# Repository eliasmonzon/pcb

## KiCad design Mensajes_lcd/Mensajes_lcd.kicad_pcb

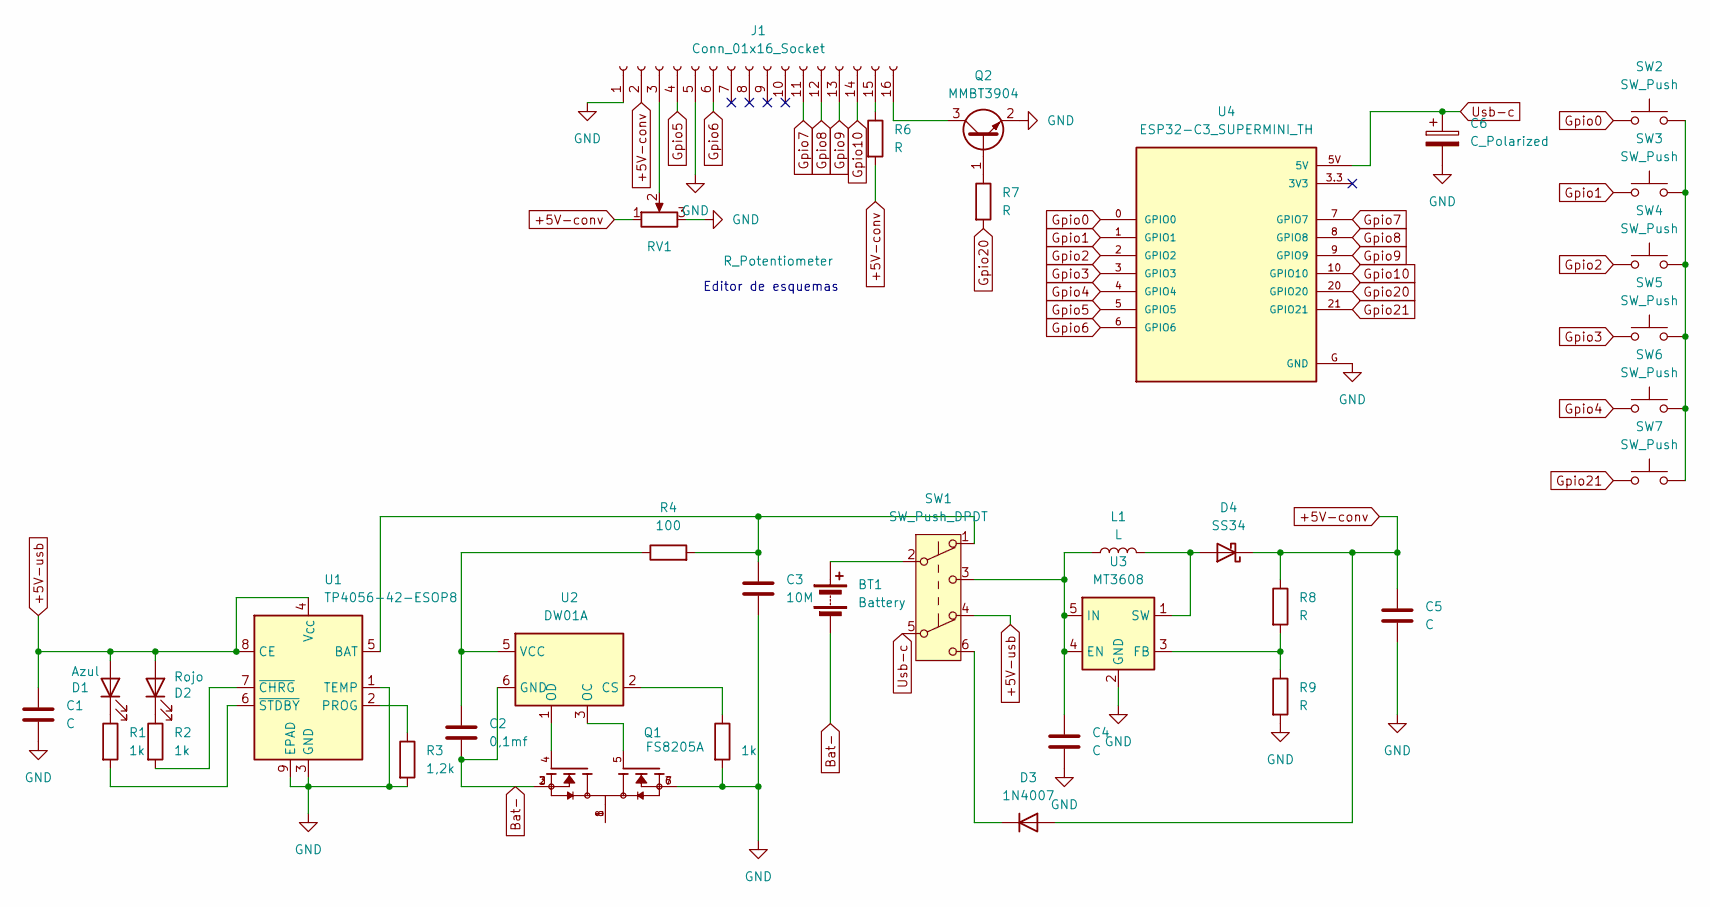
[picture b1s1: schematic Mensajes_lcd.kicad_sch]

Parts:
BT1: Battery; BatteryHolder_MPD_BH-18650-PC
C1, C4, C5: C; C_1206_3216Metric
C2: 0,1mf; C_1206_3216Metric
C3: 10M; C_1206_3216Metric
C6: C_Polarized; CP_Elec_3x5.3
D1: Azul; LED_D3.0mm
D2: Rojo; LED_D3.0mm
D3: 1N4007; D_1206_3216Metric_Pad1.42x1.75mm_HandSolder
D4: SS34; D_SMA
J1: Conn_01x16_Socket; PinHeader_1x16_P2.54mm_Vertical
L1: L; L_10.4x10.4_H4.8
Q1: FS8205A; TSSOP-8_4.4x3mm_P0.65mm; PARTREV 1.7
Q2: MMBT3904; SOT-23
R1, R2, R5: 1k; R_1206_3216Metric
R3: 1,2k; R_1206_3216Metric
R4: 100; R_1206_3216Metric
R6, R7, R8, R9: R; R_1206_3216Metric
RV1: R_Potentiometer; Potentiometer_Vishay_T73YP_Vertical
SW1: SW_Push_DPDT; SW_CK_JS202011AQN_DPDT_Angled
SW2, SW3, SW4, SW5, SW6, SW7: SW_Push; SW_SPST_Omron_B3F-40xx
U1: TP4056-42-ESOP8; SOIC-8-1EP_3.9x4.9mm_P1.27mm_EP2.29x3mm
U2: DW01A; SOT-23-6
U3: MT3608; SOT-23-6
U4: ESP32-C3_SUPERMINI_TH; MODULE_ESP32-C3_SUPERMINI_TH

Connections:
+5V-conv: C5.1, D3.2 (A), D4.1 (K), J1.2, R6.2, R8.1, RV1.1
+5V-usb: C1.1, D1.2 (A), D2.2 (A), SW1.4 (A), U1.4 (V_{CC}), U1.8 (CE)
Bat-: BT1.2 (-), C2.2, Q1.2, Q1.3, U2.6 (GND)
GND: C1.2, C3.2, C4.2, C5.2, C6.2, J1.1, J1.5, Q1.6, Q1.7, Q2.2 (E), R3.2, R5.2, R9.2, RV1.3, U1.1 (TEMP), U1.3 (GND), U1.9 (EPAD), U3.2 (GND), U4.G (GND)
Gpio0: SW2.1, U4.0 (GPIO0)
Gpio1: SW3.1, U4.1 (GPIO1)
Gpio2: SW4.1, U4.2 (GPIO2)
Gpio3: SW5.1, U4.3 (GPIO3)
Gpio4: SW6.1, U4.4 (GPIO4)
Gpio5: J1.4, U4.5 (GPIO5)
Gpio6: J1.6, U4.6 (GPIO6)
Gpio7: J1.11, U4.7 (GPIO7)
Gpio8: J1.12, U4.8 (GPIO8)
Gpio9: J1.13, U4.9 (GPIO9)
Gpio10: J1.14, U4.10 (GPIO10)
Gpio20: R7.2, U4.20 (GPIO20)
Gpio21: SW7.1, U4.21 (GPIO21)
unnamed: BT1.1 (+), SW1.2 (B)
unnamed: D1.1 (K), R1.1
unnamed: D2.1 (K), R2.1
unnamed: D3.1 (K), SW1.6 (C)
unnamed: D4.2 (A), L1.2, U3.1 (SW)
unnamed: J1.3, RV1.2
unnamed: J1.15, R6.1
unnamed: J1.16, Q2.3 (C)
unnamed: Q1.1, Q1.8
unnamed: Q2.1 (B), R7.1
unnamed: SW2.2, SW3.2, SW4.2, SW5.2, SW6.2, SW7.2
unnamed: C3.1, R4.2, SW1.1 (A), U1.5 (BAT)
unnamed: R3.1, U1.2 (PROG)
unnamed: R2.2, U1.7 (~CHRG)
unnamed: R1.2, U1.6 (~STDBY)
unnamed: R5.1, U2.2 (CS)
unnamed: Q1.5, U2.3 (OC)
unnamed: Q1.4, U2.1 (OD)
unnamed: C2.1, R4.1, U2.5 (VCC)
unnamed: C4.1, L1.1, SW1.3 (C), U3.4 (EN), U3.5 (IN)
unnamed: R8.2, R9.1, U3.3 (FB)
Usb-c: C6.1, SW1.5 (B), U4.5V

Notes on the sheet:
Editor de esquemas

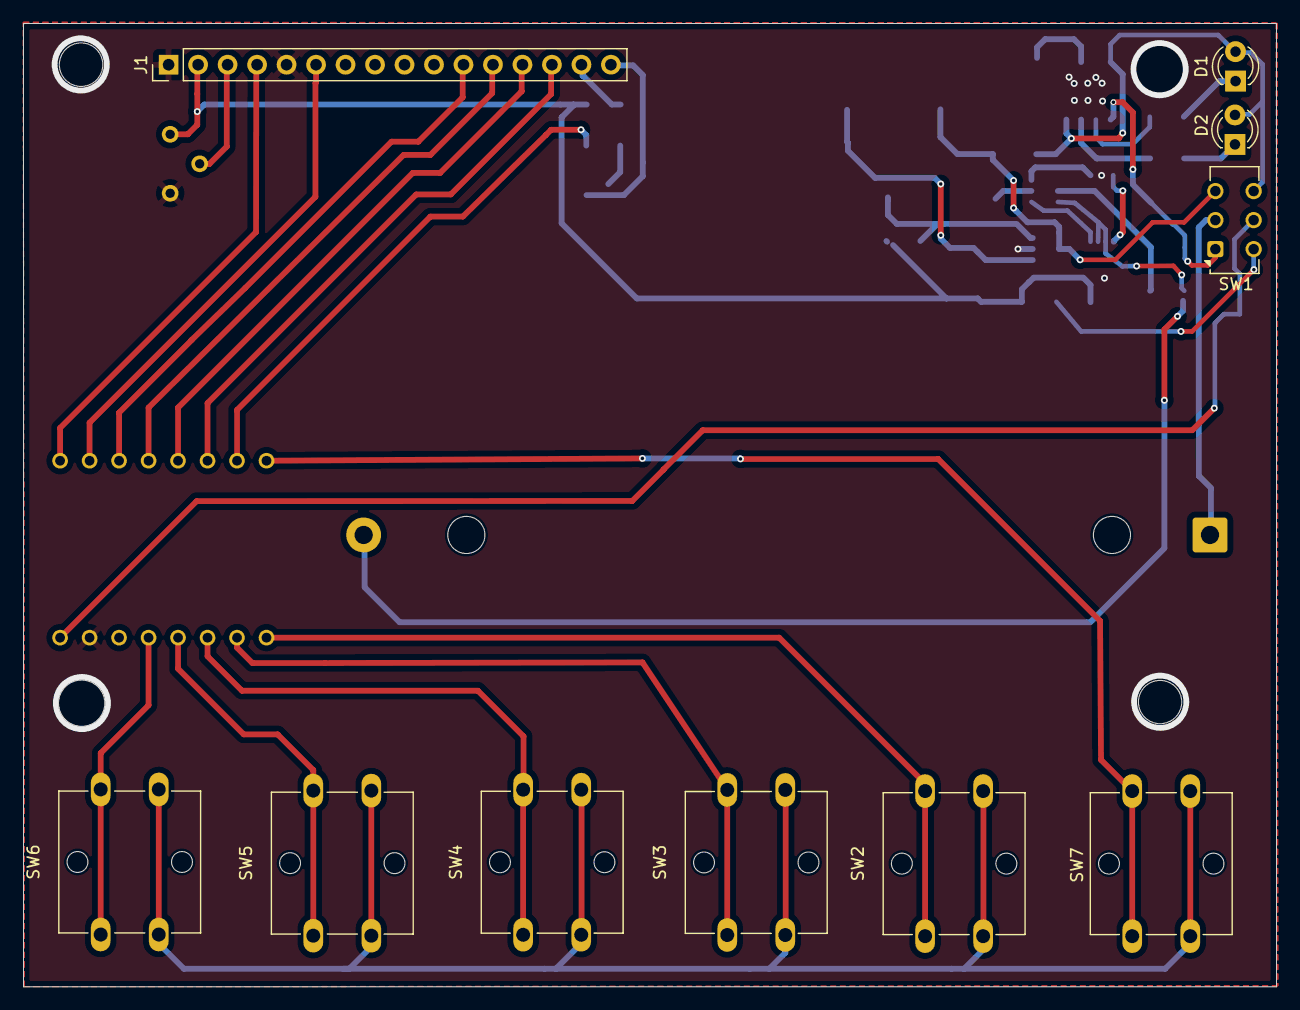
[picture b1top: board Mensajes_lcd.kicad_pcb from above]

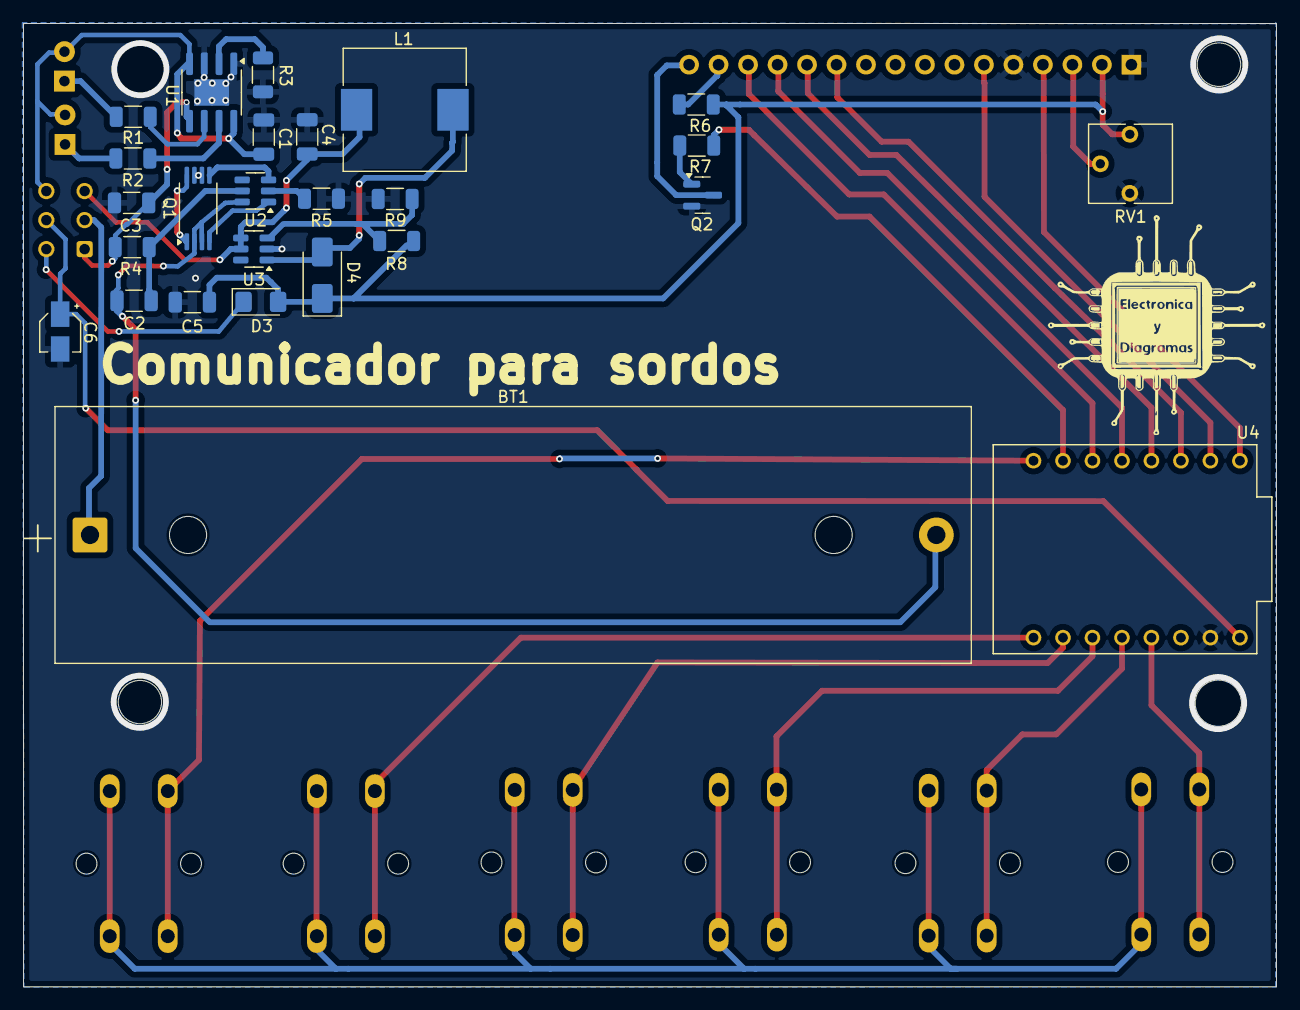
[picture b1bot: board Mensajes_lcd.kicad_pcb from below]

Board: 2 copper layers, 107.9 x 83.0 mm, 36 parts (26 on the bottom side), 39 nets.

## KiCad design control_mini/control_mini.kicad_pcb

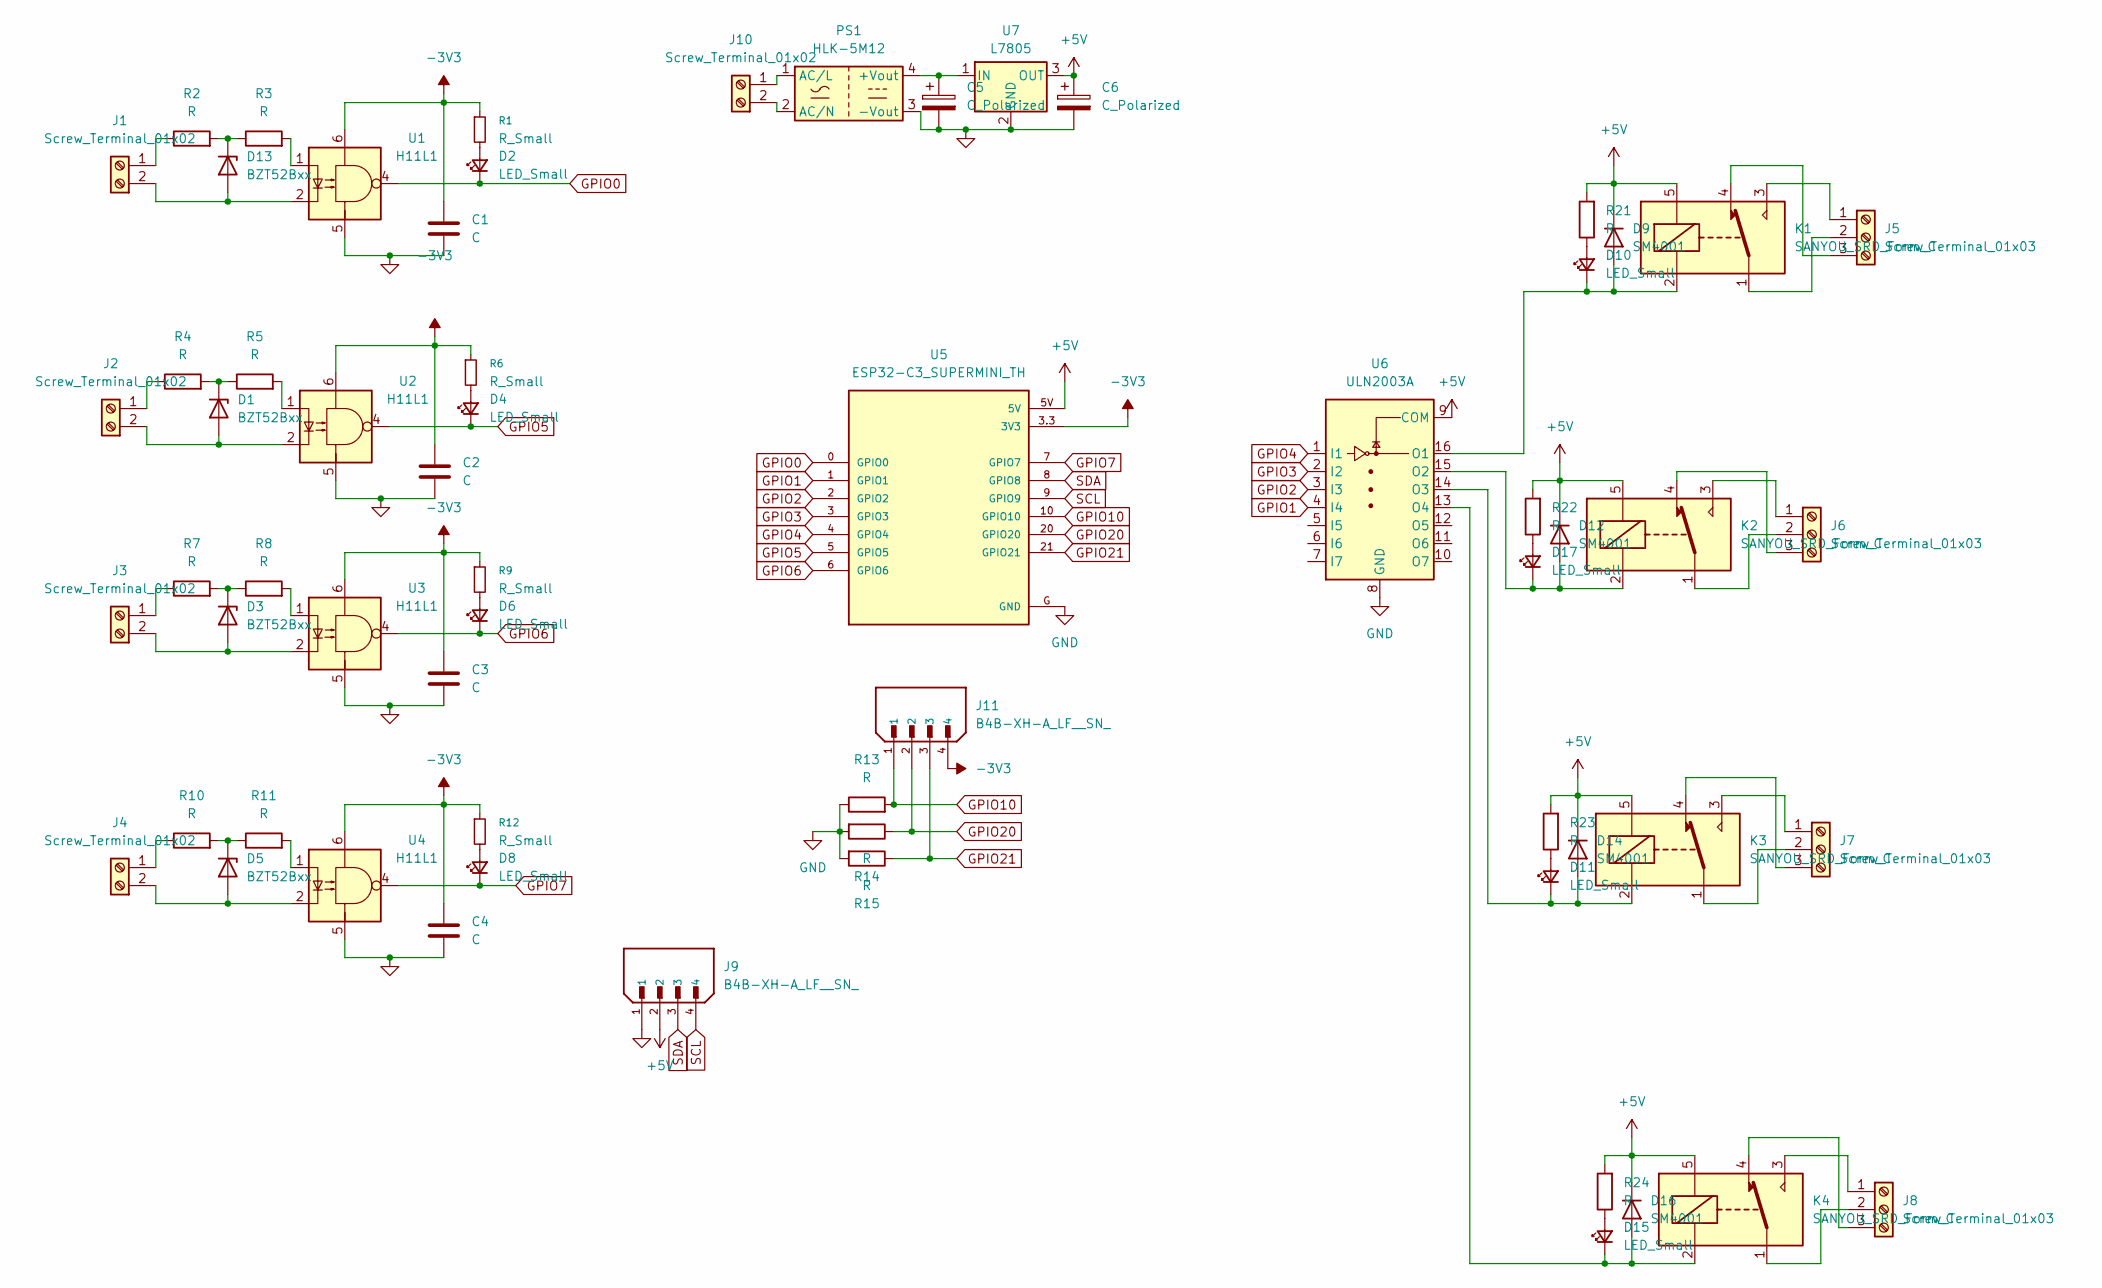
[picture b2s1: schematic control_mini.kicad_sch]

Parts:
C1, C2, C3, C4: C; C_1206_3216Metric
C5, C6: C_Polarized; CP_Elec_4x3
D1, D3, D5, D13: BZT52Bxx; D_SOD-123F
D2, D4, D6, D8, D10, D11, D15, D17: LED_Small; LED_D3.0mm
D9, D12, D14, D16: SM4001; D_SMA
J1, J2, J3, J4, J10: Screw_Terminal_01x02; TerminalBlock_Phoenix_MKDS-1,5-2-5.08_1x02_P5.08mm_Horizont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
J5, J8: Screw_Terminal_01x03; TerminalBlock_Phoenix_MKDS-1,5-3-5.08_1x03_P5.08mm_Horizont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
J6, J7: Screw_Terminal_01x03; TerminalBlock_Phoenix_MKDS-1,5-3_1x03_P5.00mm_Horizontal
J9, J11: B4B-XH-A_LF__SN_; JST_B4B-XH-A_LF__SN_; PARTREV 7/4/21
K1, K2, K3, K4: SANYOU_SRD_Form_C; Relay_SPDT_SANYOU_SRD_Series_Form_C
PS1: HLK-5M12; Converter_ACDC_Hi-Link_HLK-5Mxx
R1, R6, R9, R12: R_Small; R_1206_3216Metric
R2, R3, R4, R5, R7, R8, R10, R11, R13, R14, R15, R21, R22, R23, R24: R; R_1206_3216Metric
U1, U2, U3, U4: H11L1; DIP-6_W7.62mm
U5: ESP32-C3_SUPERMINI_TH; MODULE_ESP32-C3_SUPERMINI_TH
U6: ULN2003A; SOP-16_3.9x9.9mm_P1.27mm
U7: L7805; TO-263-2

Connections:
+5V: C6.1, D9.1 (K), D12.1 (K), D14.1 (K), D16.1 (K), J9.2, K1.5, K2.5, K3.5, K4.5, R21.2, R22.2, R23.2, R24.2, U5.5V, U6.9 (COM), U7.3 (OUT)
-3V3: C1.1, C2.1, C3.1, C4.1, J11.4, R1.1, R6.1, R9.1, R12.1, U1.6, U2.6, U3.6, U4.6, U5.3.3 (3V3)
GND: C1.2, C2.2, C3.2, C4.2, C5.2, C6.2, J9.1, PS1.3 (-Vout), R13.1, R14.2, R15.2, U1.5, U2.5, U3.5, U4.5, U5.G (GND), U6.8 (GND), U7.2 (GND)
GPIO0: D2.1 (K), U1.4, U5.0 (GPIO0)
GPIO1: U5.1 (GPIO1), U6.4 (I4)
GPIO2: U5.2 (GPIO2), U6.3 (I3)
GPIO3: U5.3 (GPIO3), U6.2 (I2)
GPIO4: U5.4 (GPIO4), U6.1 (I1)
GPIO5: D4.1 (K), U2.4, U5.5 (GPIO5)
GPIO6: D6.1 (K), U3.4, U5.6 (GPIO6)
GPIO7: D8.1 (K), U4.4, U5.7 (GPIO7)
GPIO10: J11.1, R13.2, U5.10 (GPIO10)
GPIO20: J11.2, R14.1, U5.20 (GPIO20)
GPIO21: J11.3, R15.1, U5.21 (GPIO21)
unnamed: D1.2 (A), J2.2, U2.2
unnamed: D1.1 (K), R4.2, R5.1
unnamed: D2.2 (A), R1.2
unnamed: D3.2 (A), J3.2, U3.2
unnamed: D3.1 (K), R7.2, R8.1
unnamed: D4.2 (A), R6.2
unnamed: D5.2 (A), J4.2, U4.2
unnamed: D5.1 (K), R10.2, R11.1
unnamed: D6.2 (A), R9.2
unnamed: D8.2 (A), R12.2
unnamed: D10.2 (A), R21.1
unnamed: D9.2 (A), D10.1 (K), K1.2, U6.16 (O1)
unnamed: D11.2 (A), R23.1
unnamed: D11.1 (K), D14.2 (A), K3.2, U6.14 (O3)
unnamed: D12.2 (A), D17.1 (K), K2.2, U6.15 (O2)
unnamed: D13.2 (A), J1.2, U1.2
unnamed: D13.1 (K), R2.2, R3.1
unnamed: D15.2 (A), R24.1
unnamed: D15.1 (K), D16.2 (A), K4.2, U6.13 (O4)
unnamed: D17.2 (A), R22.1
unnamed: J1.1, R2.1
unnamed: J2.1, R4.1
unnamed: J3.1, R7.1
unnamed: J4.1, R10.1
unnamed: J5.1, K1.3
unnamed: J5.2, K1.1
unnamed: J5.3, K1.4
unnamed: J6.1, K2.3
unnamed: J6.2, K2.1
unnamed: J6.3, K2.4
unnamed: J7.1, K3.3
unnamed: J7.2, K3.1
unnamed: J7.3, K3.4
unnamed: J8.1, K4.3
unnamed: J8.2, K4.1
unnamed: J8.3, K4.4
unnamed: J10.1, PS1.1 (AC/L)
unnamed: J10.2, PS1.2 (AC/N)
unnamed: C5.1, PS1.4 (+Vout), U7.1 (IN)
unnamed: R3.2, U1.1
unnamed: R5.2, U2.1
unnamed: R8.2, U3.1
unnamed: R11.2, U4.1
SCL: J9.4, U5.9 (GPIO9)
SDA: J9.3, U5.8 (GPIO8)

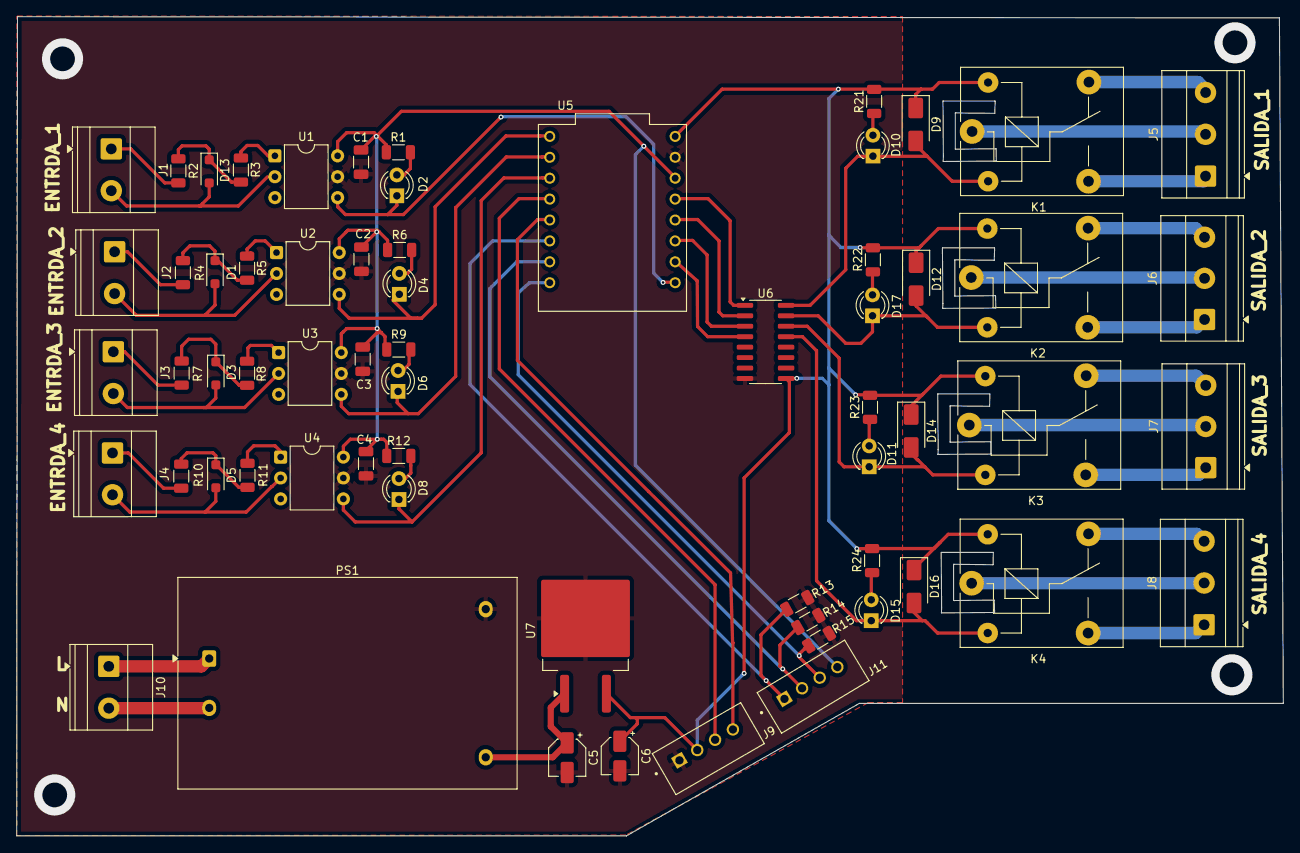
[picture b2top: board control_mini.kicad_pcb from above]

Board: 2 copper layers, 153.9 x 99.5 mm, 64 parts (0 on the bottom side), 59 nets.

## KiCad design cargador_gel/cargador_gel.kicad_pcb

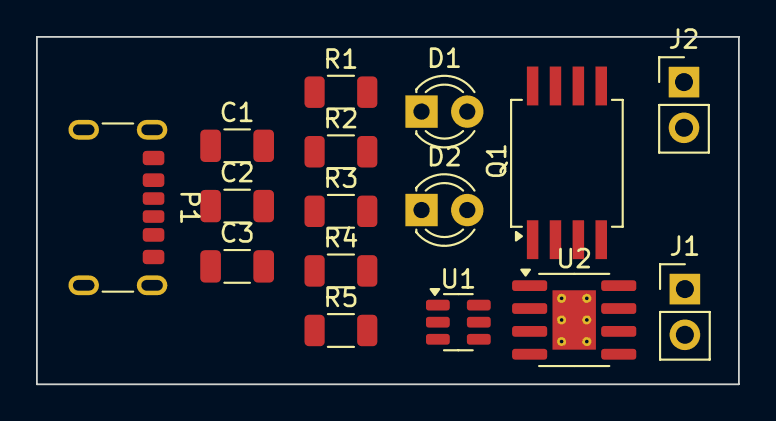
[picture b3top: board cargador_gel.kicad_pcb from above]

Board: 2 copper layers, 39.0 x 19.3 mm, 16 parts (0 on the bottom side), 13 nets, no tracks yet.

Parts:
C1, C2, C3: C; C_1206_3216Metric
D1, D2: LED; LED_D3.0mm
J1, J2: Conn_01x02_Pin; PinHeader_1x02_P2.54mm_Vertical
P1: USB_C_Plug_USB2.0; USB_C_Receptacle_GCT_USB4125-xx-x-0190_6P_TopMnt_Horizontal
Q1: FS8205A; SSO-8_6.8x5.9mm_P1.27mm_Clearance7mm
R1, R2, R3, R4, R5: R; R_1206_3216Metric
U1: DW01A; SOT-23-6
U2: TP4056-42-ESOP8; SOIC-8-1EP_3.9x4.9mm_P1.27mm_EP2.41x3.3mm_ThermalVias

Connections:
GND: C1.2, C2.2, C3.2, J2.1, P1.A12 (GND), P1.B12 (GND), Q1.2, Q1.3, R5.2, U1.6 (GND), U2.1 (TEMP), U2.3 (GND)
unnamed: C2.1, C3.1, D1.2 (A), D2.2 (A), J1.1, J1.2, P1.A9 (VBUS), P1.B9 (VBUS), R2.2, U2.4 (V_{CC}), U2.8 (CE)
unnamed: D1.1 (K), R3.1
unnamed: D2.1 (K), R4.1
unnamed: J2.2, Q1.6, Q1.7, R1.2
unnamed: Q1.1, Q1.8
unnamed: R1.1, U1.2 (CS)
unnamed: Q1.5, U1.3 (OC)
unnamed: Q1.4, U1.1 (OD)
unnamed: C1.1, R2.1, U1.5 (VCC)
unnamed: R5.1, U2.2 (PROG)
unnamed: R3.2, U2.7 (~CHRG)
unnamed: R4.2, U2.6 (~STDBY)

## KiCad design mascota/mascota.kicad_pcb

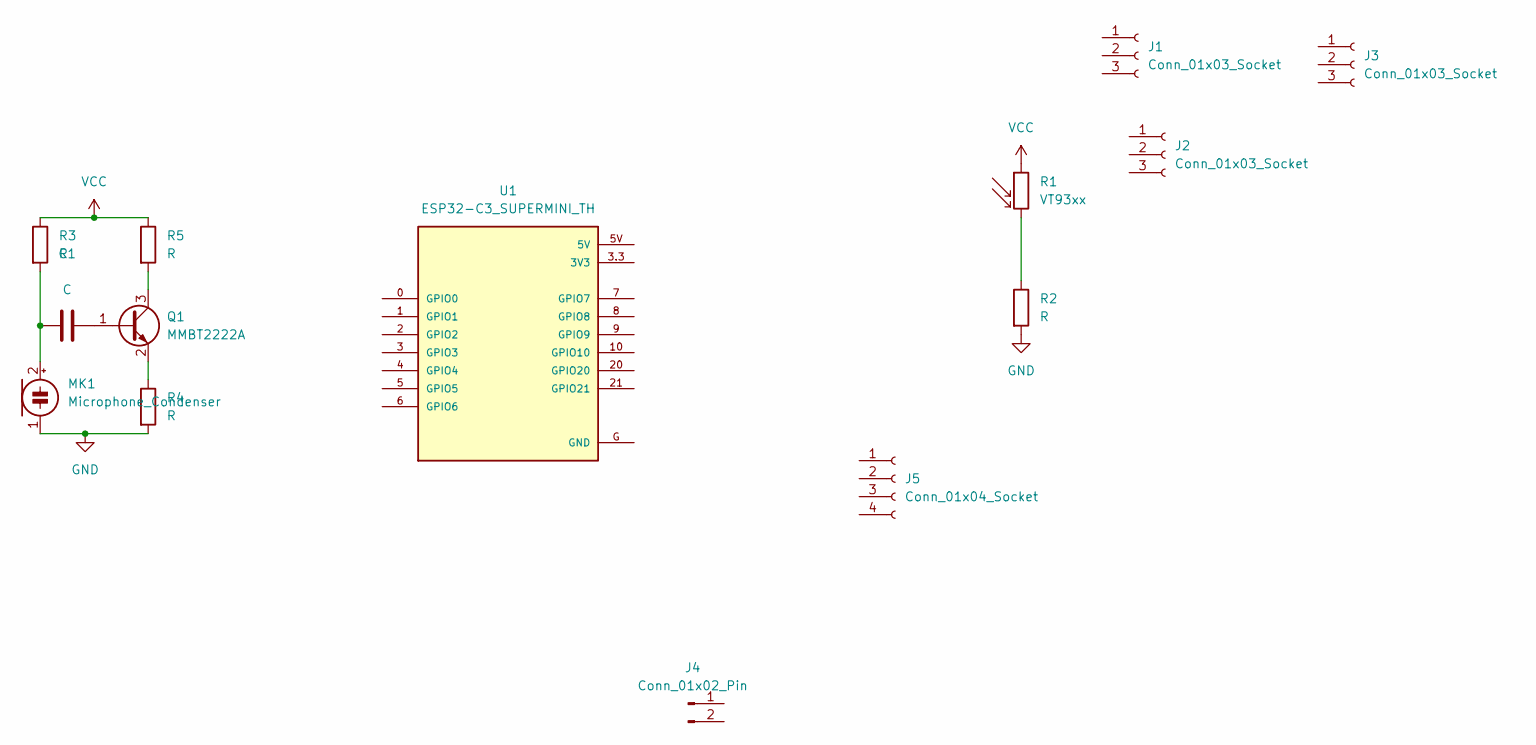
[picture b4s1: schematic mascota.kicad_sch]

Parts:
C1: C; C_1206_3216Metric
J1, J2: Conn_01x03_Socket; PinSocket_1x03_P2.54mm_Horizontal
J3: Conn_01x03_Socket; PinSocket_1x03_P2.54mm_Vertical
J4: Conn_01x02_Pin; PinHeader_1x02_P2.54mm_Horizontal
J5: Conn_01x04_Socket; PinSocket_1x04_P2.54mm_Vertical
MK1: Microphone_Condenser; POM-2244P-C3310-2-R
Q1: MMBT2222A; SOT-23
R1: VT93xx; R_LDR_4.9x4.2mm_P2.54mm_Vertical
R2, R3, R4, R5: R; R_1206_3216Metric_Pad1.30x1.75mm_HandSolder
U1: ESP32-C3_SUPERMINI_TH; MODULE_ESP32-C3_SUPERMINI_TH

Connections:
GND: MK1.1 (-), R2.2, R4.2
unnamed: C1.1, MK1.2 (+), R3.2
unnamed: C1.2, Q1.1 (B)
unnamed: Q1.3 (C), R5.2
unnamed: Q1.2 (E), R4.1
unnamed: R1.2, R2.1
VCC: R1.1, R3.1, R5.1

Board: 2 copper layers, 14 parts (0 on the bottom side), 7 nets, no tracks yet.

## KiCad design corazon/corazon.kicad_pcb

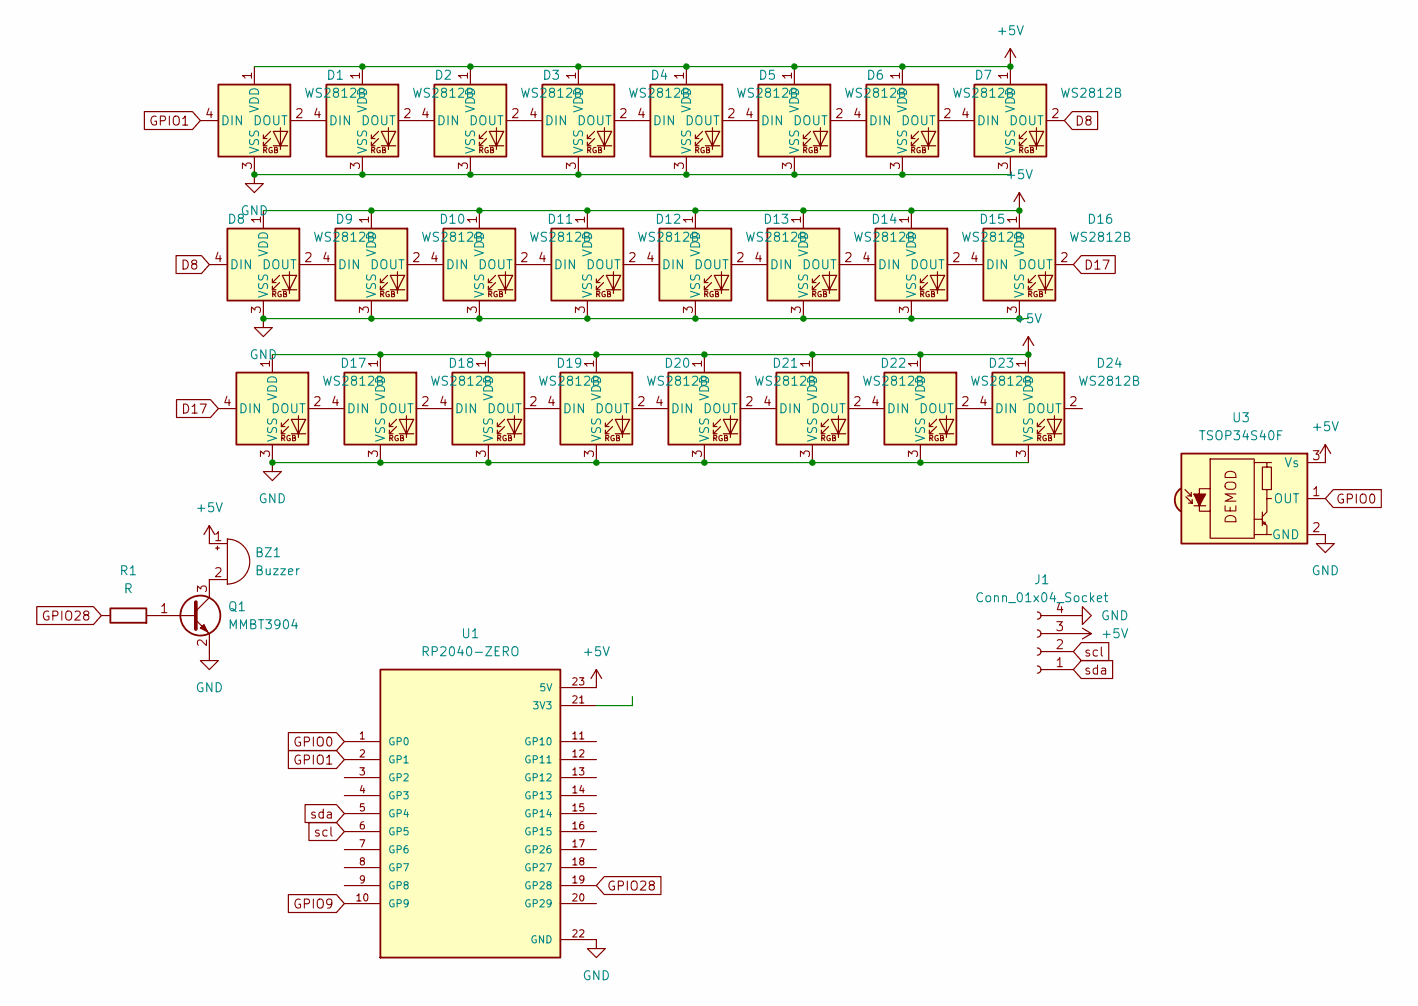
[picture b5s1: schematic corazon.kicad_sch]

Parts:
BZ1: Buzzer; Buzzer_12x9.5RM7.6
D1, D2, D3, D4, D5, D6, D7, D8, D9, D10, D11, D12, D13, D14, D15, D16, D17, D18, D19, D20, D21, D22, D23, D24: WS2812B; LED_WS2812B_PLCC4_5.0x5.0mm_P3.2mm
J1: Conn_01x04_Socket; PinHeader_1x04_P2.54mm_Vertical
Q1: MMBT3904; SOT-23
R1: R; R_1206_3216Metric
U1: RP2040-ZERO; MODULE_RP2040-ZERO; PARTREV NA
U3: TSOP34S40F; Vishay_MOLD-3Pin

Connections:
+5V: BZ1.1 (+), D1.1 (VDD), D2.1 (VDD), D3.1 (VDD), D4.1 (VDD), D5.1 (VDD), D6.1 (VDD), D7.1 (VDD), D8.1 (VDD), D9.1 (VDD), D10.1 (VDD), D11.1 (VDD), D12.1 (VDD), D13.1 (VDD), D14.1 (VDD), D15.1 (VDD), D16.1 (VDD), D17.1 (VDD), D18.1 (VDD), D19.1 (VDD), D20.1 (VDD), D21.1 (VDD), D22.1 (VDD), D23.1 (VDD), D24.1 (VDD), J1.3, U1.23 (5V), U3.3 (Vs)
D8: D8.2 (DOUT), D9.4 (DIN)
D17: D16.2 (DOUT), D17.4 (DIN)
GND: D1.3 (VSS), D2.3 (VSS), D3.3 (VSS), D4.3 (VSS), D5.3 (VSS), D6.3 (VSS), D7.3 (VSS), D8.3 (VSS), D9.3 (VSS), D10.3 (VSS), D11.3 (VSS), D12.3 (VSS), D13.3 (VSS), D14.3 (VSS), D15.3 (VSS), D16.3 (VSS), D17.3 (VSS), D18.3 (VSS), D19.3 (VSS), D20.3 (VSS), D21.3 (VSS), D22.3 (VSS), D23.3 (VSS), D24.3 (VSS), J1.4, Q1.2 (E), U1.22 (GND), U3.2 (GND)
GPIO0: U1.1 (GP0), U3.1 (OUT)
GPIO1: D1.4 (DIN), U1.2 (GP1)
GPIO9: U1.10 (GP9)
GPIO28: R1.1, U1.19 (GP28)
unnamed: BZ1.2 (-), Q1.3 (C)
unnamed: D1.2 (DOUT), D2.4 (DIN)
unnamed: D2.2 (DOUT), D3.4 (DIN)
unnamed: D3.2 (DOUT), D4.4 (DIN)
unnamed: D4.2 (DOUT), D5.4 (DIN)
unnamed: D5.2 (DOUT), D6.4 (DIN)
unnamed: D6.2 (DOUT), D7.4 (DIN)
unnamed: D7.2 (DOUT), D8.4 (DIN)
unnamed: D9.2 (DOUT), D10.4 (DIN)
unnamed: D10.2 (DOUT), D11.4 (DIN)
unnamed: D11.2 (DOUT), D12.4 (DIN)
unnamed: D12.2 (DOUT), D13.4 (DIN)
unnamed: D13.2 (DOUT), D14.4 (DIN)
unnamed: D14.2 (DOUT), D15.4 (DIN)
unnamed: D15.2 (DOUT), D16.4 (DIN)
unnamed: D17.2 (DOUT), D18.4 (DIN)
unnamed: D18.2 (DOUT), D19.4 (DIN)
unnamed: D19.2 (DOUT), D20.4 (DIN)
unnamed: D20.2 (DOUT), D21.4 (DIN)
unnamed: D21.2 (DOUT), D22.4 (DIN)
unnamed: D22.2 (DOUT), D23.4 (DIN)
unnamed: D23.2 (DOUT), D24.4 (DIN)
unnamed: Q1.1 (B), R1.2
scl: J1.2, U1.6 (GP5)
sda: J1.1, U1.5 (GP4)

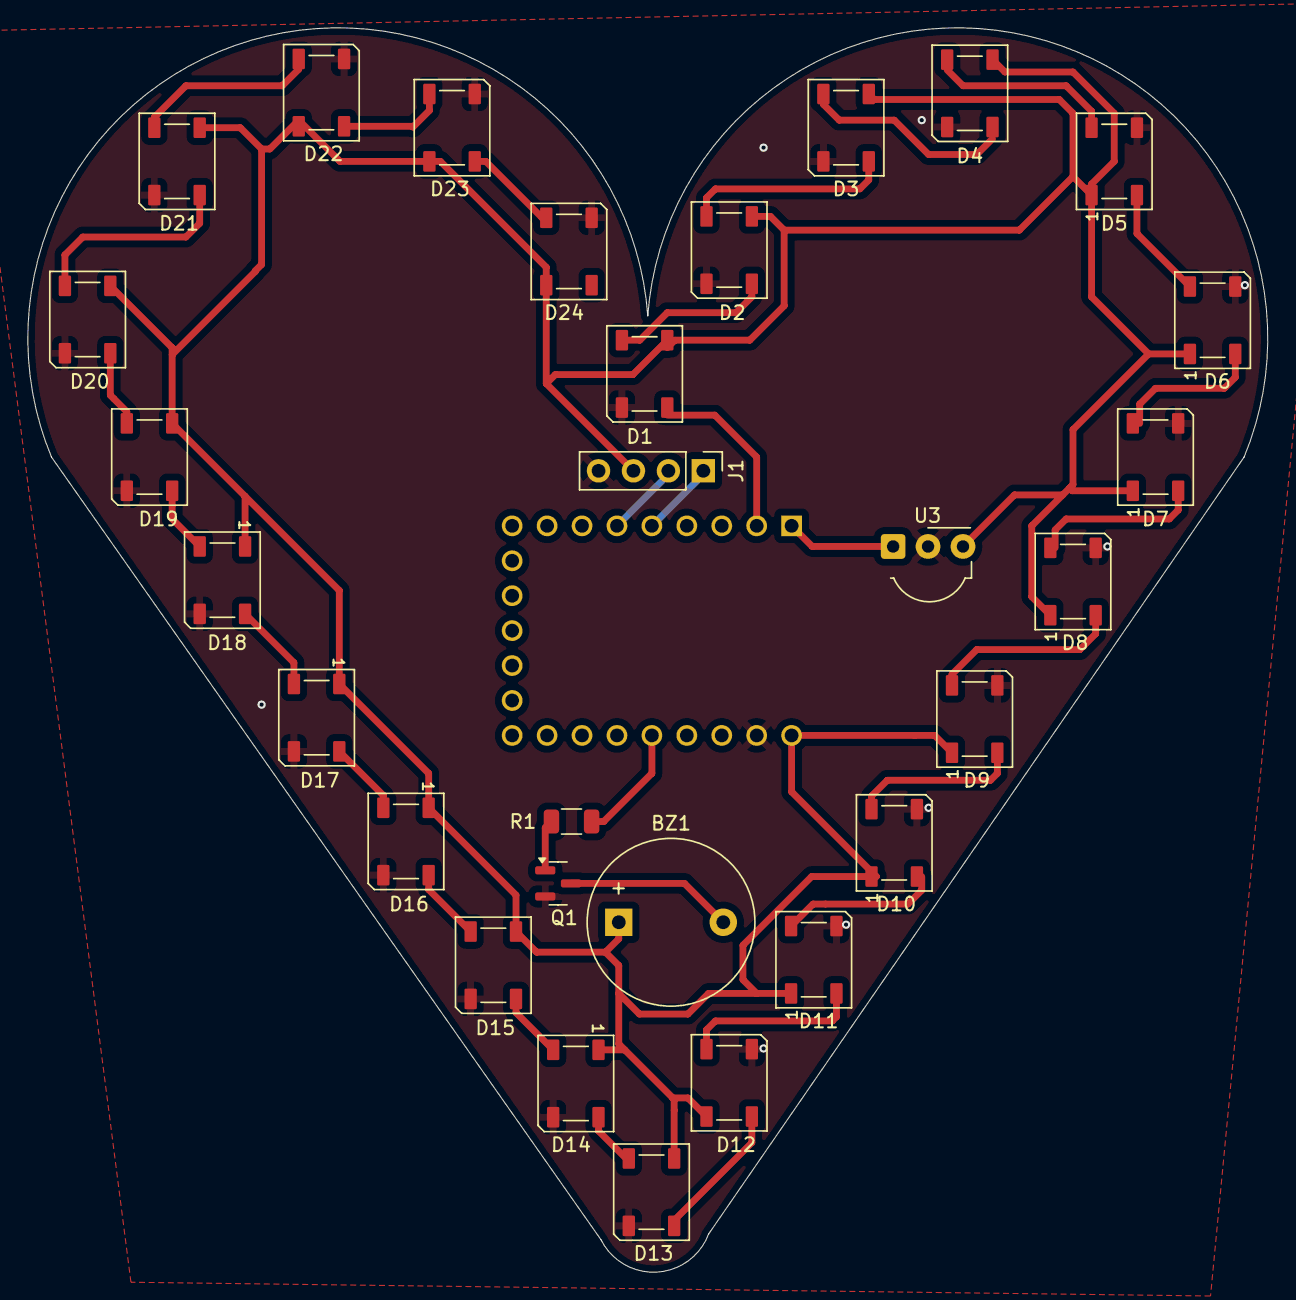
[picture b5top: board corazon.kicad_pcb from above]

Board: 2 copper layers, 90.2 x 90.5 mm, 30 parts (1 on the bottom side), 32 nets.
